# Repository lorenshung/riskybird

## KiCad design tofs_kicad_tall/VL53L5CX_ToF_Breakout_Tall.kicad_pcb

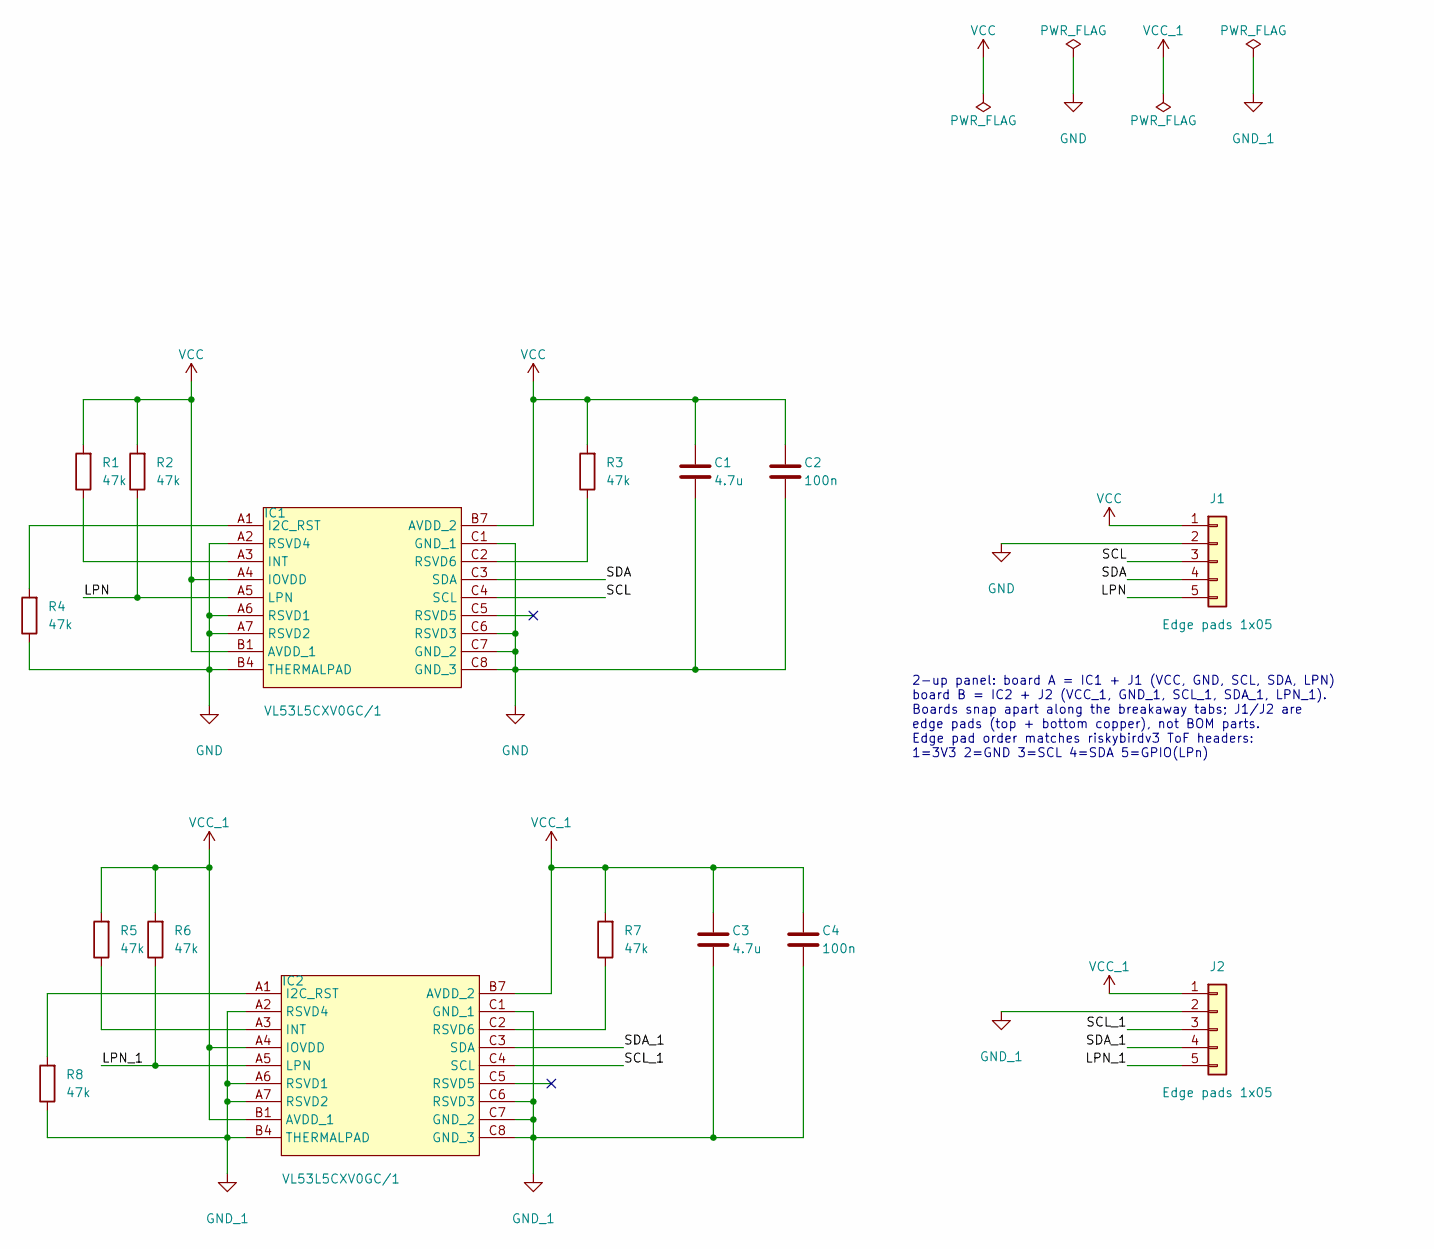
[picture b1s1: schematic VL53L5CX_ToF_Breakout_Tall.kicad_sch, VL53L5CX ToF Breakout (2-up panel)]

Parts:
C1, C3: 4.7u; C_0402_1005Metric; MPN CC0402KRX5R6BB475
C2, C4: 100n; C_0402_1005Metric; MPN CC0402KRX7R7BB104
IC1, IC2: VL53L5CXV0GC/1; ST_VL53L5CXV0GC1; MPN VL53L5CXV0GC/1
J1, J2: Edge pads 1x05; EdgePads_1x05_P2.54mm_DoubleSided
R1, R2, R3, R4, R5, R6, R7, R8: 47k; R_0402_1005Metric; MPN RC0402FR-0747KL

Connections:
/LPN: IC1.A5 (LPN), J1.5, R2.1
/LPN_1: IC2.A5 (LPN), J2.5, R6.1
/SCL: IC1.C4 (SCL), J1.3
/SCL_1: IC2.C4 (SCL), J2.3
/SDA: IC1.C3 (SDA), J1.4
/SDA_1: IC2.C3 (SDA), J2.4
GND: C1.2, C2.2, IC1.A2 (RSVD4), IC1.A6 (RSVD1), IC1.A7 (RSVD2), IC1.B4 (THERMALPAD), IC1.C1 (GND_1), IC1.C6 (RSVD3), IC1.C7 (GND_2), IC1.C8 (GND_3), J1.2, R4.1
GND_1: C3.2, C4.2, IC2.A2 (RSVD4), IC2.A6 (RSVD1), IC2.A7 (RSVD2), IC2.B4 (THERMALPAD), IC2.C1 (GND_1), IC2.C6 (RSVD3), IC2.C7 (GND_2), IC2.C8 (GND_3), J2.2, R8.1
unnamed: IC1.A1 (I2C_RST), R4.2
unnamed: IC1.A3 (INT), R1.1
unnamed: IC1.C2 (RSVD6), R3.1
unnamed: IC2.A1 (I2C_RST), R8.2
unnamed: IC2.A3 (INT), R5.1
unnamed: IC2.C2 (RSVD6), R7.1
VCC: C1.1, C2.1, IC1.A4 (IOVDD), IC1.B1 (AVDD_1), IC1.B7 (AVDD_2), J1.1, R1.2, R2.2, R3.2
VCC_1: C3.1, C4.1, IC2.A4 (IOVDD), IC2.B1 (AVDD_1), IC2.B7 (AVDD_2), J2.1, R5.2, R6.2, R7.2

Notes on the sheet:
2-up panel: board A = IC1 + J1 (VCC, GND, SCL, SDA, LPN) board B = IC2 + J2 (VCC_1, GND_1, SCL_1, SDA_1, LPN_1). Boards snap apart along the breakaway tabs; J1/J2 are edge pads (top + bottom copper), not BOM parts. Edge pad order matches riskybirdv3 ToF headers: 1=3V3 2=GND 3=SCL 4=SDA 5=GPIO(LPn)

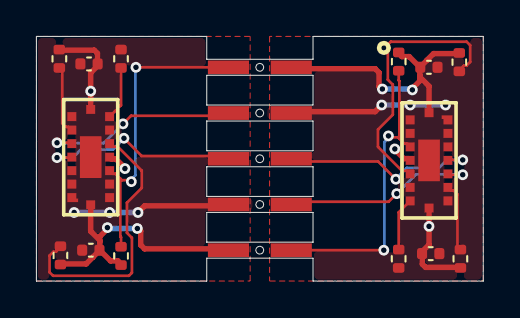
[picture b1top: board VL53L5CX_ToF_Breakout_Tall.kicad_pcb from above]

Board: 2 copper layers, 24.8 x 13.6 mm, 17 parts (0 on the bottom side), 16 nets.

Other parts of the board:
TAB1: BreakawayTab_Holes; BreakawayTab_Holes_1x05_P2.54mm_D0.43mm
